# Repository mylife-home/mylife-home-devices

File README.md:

# mylife-home-devices
MyLife Home devices

- [ePanel IO](epanel-io/README.md) :white_check_mark: Module de tableau électrique pour interconnecter E/S avec domotique (rpi/esp)
- [ePanel Energy Monitor](epanel-energy-monitor/README.md) :white_check_mark: Module de tableau électrique pour mesurer la consommation électrique
- [ePanel Controller](epanel-controller/README.md) :white_check_mark: Module de tableau électrique pour contrôler IO et Energy Monitor
- [Garden box](garden-box/README.md) :white_check_mark: Boîtier de commandes/capteurs dans le jardin
- [RGB garden box](rgb-garden-box/README.md) :white_check_mark: Boîtier de commande spots RGB dans le jardin
- [RGB spot 10W](rgb-spot-10w/README.md) :white_check_mark: Reprise de spots existant infrarouge pour connexion direct cables RGB
- [Garage door driver](garage-door-driver/README.md) :white_check_mark: Pilote de porte de garage
- [Clim driver](clim-driver/README.md) :white_check_mark: Pilote de clim
- [Gate driver](gate-driver/README.md) :hourglass: Pilote de portail
- [Bed Smart Plug](bed-smart-plug/README.md) :white_check_mark: "Multiprise intelligente" pour mettre en tête de lit
- [Presence Wifi sensor](presence-wifi-sensor/README.md) :question: Détecteur de présence Wifi
- [RGB LED inverter](rgb-led-inverter/README.md) :no_entry: common anode -> common cathode
- RGB indoor box :question: Boîtier de commande spots/ruban leds RGB en intérieur
- Kitchen hood driver :question: Pilote de hôte
- Pergola driver :question: Pilote de pergola (ZETA 868 ?)
- [Fairy lights](fairy-lights/README.md): :hourglass: guirlande de noël
- [Heater driver](heater-driver/README.md): :question: pilote de radiateur
- [Deco light](deco-light/README.md): :question: Lumière de décoration

## Notes
- Tutorial KiCad: https://www.youtube.com/playlist?list=PLuQznwVAhY2WA4CIf3_aB_e8hRCSbQuUp
- Best practice routing PCB: https://resources.altium.com/fr/p/top-5-pcb-design-guidelines-every-pcb-designer-needs-know
- Kicad to JLCPCB
  - https://support.jlcpcb.com/article/149-how-to-generate-gerber-and-drill-files-in-kicad
  - https://support.jlcpcb.com/article/84-how-to-generate-the-bom-and-centroid-file-from-kicad
  - plugin pour aide a la generation de commande : https://github.com/Bouni/kicad-jlcpcb-tools
  - plugin pour importer les composants JLCPCB dans Kicad : https://github.com/TousstNicolas/JLC2KiCad_lib
- Component footprints : https://componentsearchengine.com/
- ESP32-POE:
  - NE PAS utiliser GPIO0 si possible (ne pas le mettre DOWN au boot)
  - Attention : Version avec antenne interne est plus grande (pas que l'ESP, toute la board). Le footprint Kicad courant correspond à la version avec antenne externe : 
- ESP8266 strapping pins:
  - GPIO0, GPIO1, GPIO2: boot failure if pulled LOW
  - GPIO15: boot failure if pulled HIGH
  - GPIO1, GPIO2, GPIO3, GPIO9, GPIO10, GPIO16: pin is high at BOOT

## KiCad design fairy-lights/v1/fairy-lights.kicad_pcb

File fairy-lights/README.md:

# Fairy lights

## Besoin

- Avec Eléonore
- Guirlande pour sapin
- Intégré ESPHome

## Design

- Guirlande :
  - WS2812B
  - https://amzn.eu/d/6PvWFXF
  - ( https://www.adafruit.com/product/4917 )
- Contrôleur :
  - WeMos D1 mini, sur gpio3 pour DMA
  - config esphome dma -> GPIO3 - RX
- Alimentation :
  - Puissance guirlande : Alim 5V 6A -> 60ma / led
  - ~alim 6A (69.5x39x24) : https://fr.rs-online.com/web/p/alimentations-a-decoupage/1358945~
  - ~alim 8A (87x52x29.5) : https://fr.rs-online.com/web/p/alimentations-a-decoupage/1358955~
  - alime externe 5V 8A : https://www.amazon.fr/dp/B088FBXTPS : `+` au milieu `-` à l'extérieur, 5.5mm - 2.5mm
  - Connecteur : 
    - https://fr.rs-online.com/web/p/connecteurs-d-alimentation-dc/2832406 - 283-2406
    - ( https://fr.rs-online.com/web/p/connecteurs-d-alimentation-dc/8782606 )
- IRLZ44N pour switch l'alim (sans heatsink), sortie esp direct sur Din LEDs : https://fr.rs-online.com/web/p/transistors-mosfet/5410086 541-0086
- Boitier : https://fr.rs-online.com/web/p/boitiers-pour-usage-general/9190373 - 919-0373

## V1

### Wiring

- `+` -> fil avec points noirs
- `D` -> fil du milieu
- `-` -> fil de l'autre côté 

### 3D view

### Main

### Images

## Prototype 1

- Sur breadboard
- Verifier qu'on peut piloter la guirlande avec esp8366/esphome

### Pinout de la guirlande

- `+` -> fil avec points noirs
- `D` -> fil du milieu
- `-` -> fil de l'autre côté

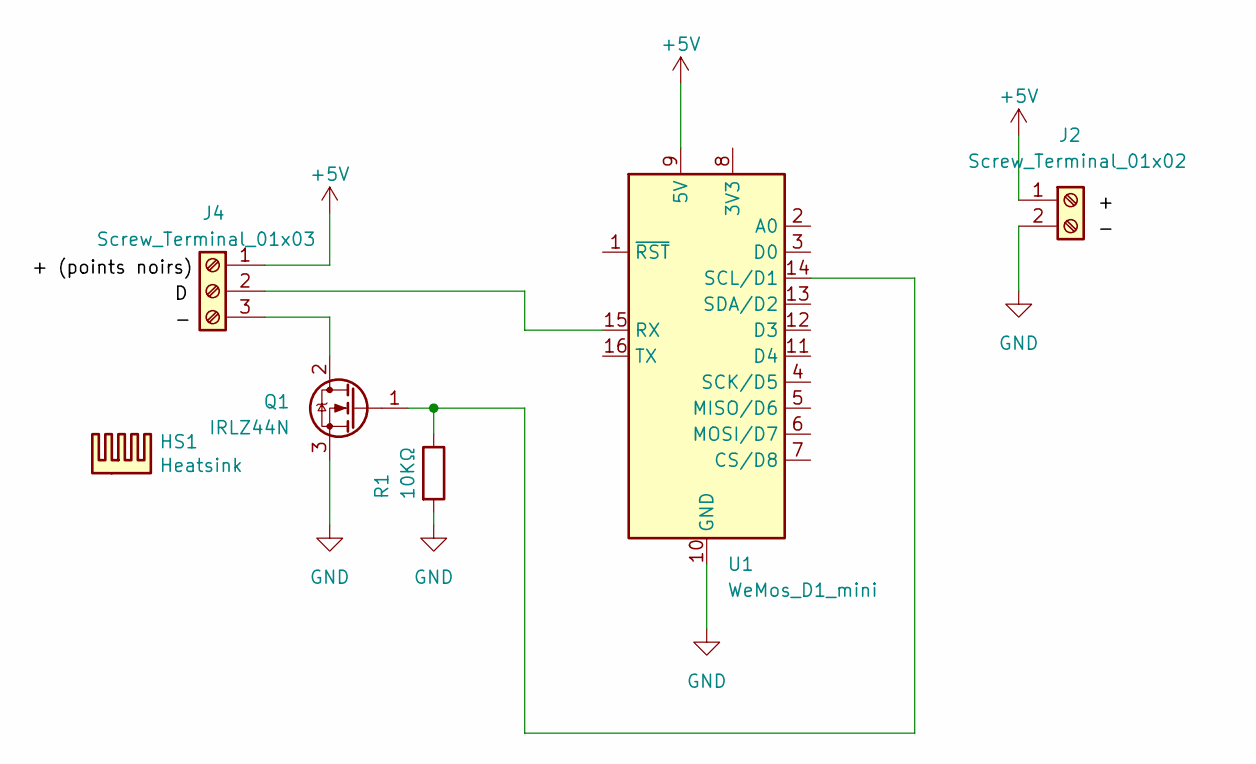
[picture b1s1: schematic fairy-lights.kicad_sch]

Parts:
HS1: Heatsink; Heatsink_Fischer_SK104-STC-STIC_35x13mm_2xDrill2.5mm
J2: Screw_Terminal_01x02; TerminalBlock_bornier-2_P5.08mm
J4: Screw_Terminal_01x03; TerminalBlock_bornier-3_P5.08mm
Q1: IRLZ44N; TO-220-3_Vertical
R1: 10KΩ; R_Axial_DIN0207_L6.3mm_D2.5mm_P15.24mm_Horizontal
U1: WeMos_D1_mini; WEMOS_D1_mini_light

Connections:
+5V: J2.1, J4.1, U1.9 (5V)
GND: J2.2, Q1.3 (S), R1.2, U1.10 (GND)
unnamed: J4.2, U1.15 (RX)
unnamed: J4.3, Q1.2 (D)
unnamed: Q1.1 (G), R1.1, U1.14 (SCL/D1)

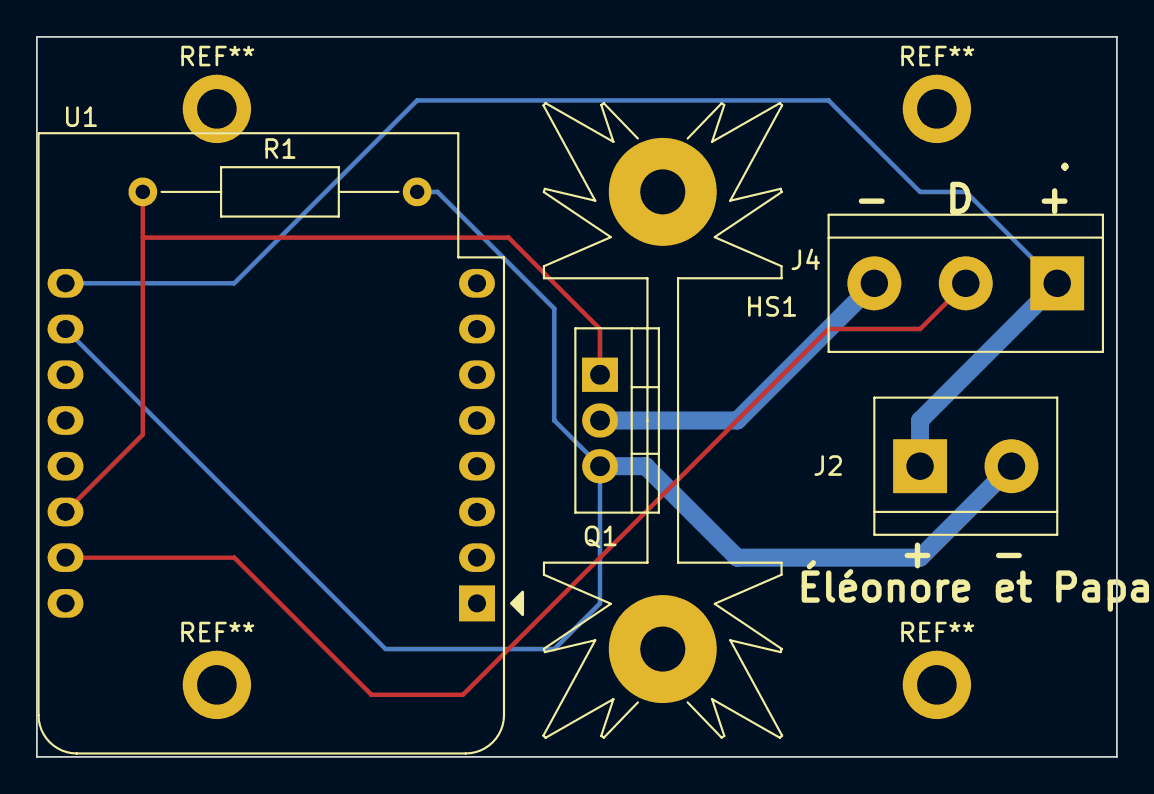
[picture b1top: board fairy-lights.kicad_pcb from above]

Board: 2 copper layers, 60.0 x 40.0 mm, 6 parts (0 on the bottom side), 5 nets.

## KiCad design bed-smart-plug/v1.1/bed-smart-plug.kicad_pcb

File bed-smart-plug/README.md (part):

# Bed Smart Plug

## Besoin

- Récepteur 433mhz (pour télécommande)
- Capteur température
- 4 sorties prises entre 5W et 200W
- Wifi et Ethernet
- Boitier :
  - peut etre relativement large/long, mais plat
  - avec les prises sur un côté
  - comme un switch
  - comme ca on peut le mettre sous un meuble, ou derriere un meuble debout

### Emplacements

- chambre parents
- chambre Eléonore
- chambre Éloïse
- chambre d'amis ?
- rdc derrière TV ?
- bibliothèque pour lampe pot de fleurs + température ?

## Choix techniques

- ESP32 ethernet ou wifi
  - prévoir des trous sur le PCB pour fixer l'esp avec un serre flex entre son header et son module ESP, sur l'inscription "ESP32-PoE"
- SSR pour éviter claquement relais
  - BT136 (4A max)
  - Dissipateurs
  - Fusible 5x20 à souder
- Entree Prise alim IEC C14
- Sorties prises IEC C13 pour avoir un format plus compact
- Capteur température :
  - DS18b20
  - avec Jack
  - possible souder jack a la main sinon
  - capteur integré inutile (mesure la temperature de l'esp/des triac pas de la piece)
- Télécommande 433MHz:
  - Renkforce 1208459
  - https://amzn.eu/d/fGBrWJP
  - https://www.conrad.fr/fr/p/renkforce-1208459-sans-fil-telecommande-interieure-1208459.html

## Design

- Board : ESP32-POE https://www.olimex.com/Products/IoT/ESP32/ESP32-POE/open-source-hardware
- Alim 220v -> 5V 1A : 
  - ~~https://fr.rs-online.com/web/p/alimentations-a-decoupage/1812200~~ (n'existe plus)
  - https://fr.rs-online.com/web/p/alimentations-a-decoupage/1359226
- Jack DS18B20 :
  - https://www.amazon.fr/dp/B075FYYLLV/
  - https://fr.rs-online.com/web/p/connecteurs-jacks/5051299
- Récepteur 433MHz : (modulation ASK)
  - ~~AM-RX12A-433P https://fr.farnell.com/rf-solutions/am-rx12a-433p/recepteur-module-rf-433-92-110dbm/dp/2759279~~ (frais de gestion trop chers)
  - QAM-RX10-433 https://fr.rs-online.com/web/p/modules-rf/1258208
  - pinout compatible
  - normalement 5V, tester en broadboard avec alim 5V + pont diviseur sur les data pour passer a 3.3V
- Triac : BT136-600E https://fr.rs-online.com/web/p/triac/7271120
  - ~~Dissipateur https://fr.rs-online.com/web/p/dissipateurs-de-chaleur/1898101/~~
  - moins haut, même base : https://fr.rs-online.com/web/p/dissipateurs-de-chaleur/1898094
  - vis M3 : même que garden box : https://fr.rs-online.com/web/p/vis-a-rondelle-indesserrable/0279149
  - écrous M3 : https://fr.rs-online.com/web/p/ecrous-hexagonaux/0560293
- Porte fusible : https://fr.rs-online.com/web/p/porte-fusibles/1769047
  - Fusible : https://fr.rs-online.com/web/p/fusibles-cartouches/6686007
- Boitier :
  - https://fr.rs-online.com/web/p/boitiers-pour-usage-general/8180494
    - noir comme les connecteurs C13/C14
    - les facades laterales sont d'un seul tenant: le couvercle est "plat", plus facile pour percer les facades.
  - Vis de fixation PCB : https://fr.rs-online.com/web/p/vis-autotaraudeuses/4831202
- Prises :
  - ~~entree C14 : https://fr.rs-online.com/web/p/connecteurs-iec/8117207~~
  - ~~sortie C13 : https://fr.rs-online.com/web/p/connecteurs-iec/8117193~~
  - sortie C13 x 4 à clip : https://fr.rs-online.com/web/p/connecteurs-iec/2318101
    - couper une barre (phase), laisser les 2 autres
    - montage :

  - entrée C13 à clip : https://fr.rs-online.com/web/p/connecteurs-iec/0481623
    - montage :

  - ~~1 entrée 4 sorties : https://fr.rs-online.com/web/p/connecteurs-iec/3135474~~
    - semble indisponible

  - Prise C14 pour câbles : https://amzn.eu/d/47d2yMY

## Observations Prototype-1 epanel-io

- cf [epanel-io/README.md#observations](../epanel-io/README.md#observations) - Triac
- si on enleve snubber du phototriac, toujours une fuite (couper la piste entre C3 et C4)
- si on enleve les 2 snubbers, plus de fuite, spot led 10w reste eteint (couper la piste entre C3 et le triac)

## Prototype-1

### Objectifs

- Triac: 
  - dissipateurs
  - snubbers/bruit/fuite
    - spot 10w
    - guirlande boules
    - lampe bureau
    - lampe chevet
    - alim a decoupage
- 433MHz receiver
  - binding avec telecommandes
- ds18b20
  - jack pinout: voir quelles broches sur chaque prise matchent + selectionner le pinout qu'on veut.
- fusibles

### Schematic

- [Schematic](prototype-1/schematic.png)

### Pinout

- GPIO02 : Triac
- GPIO13 : DS18B20
- GPIO36 : Récepteur 433MHz

### Observations

- Dissipateur :
  - Rapprocher dissipateur et triac de 0.5 - 1 mm
  - Fixation dissipateur/triac : écrou M3 + reprendre vis M3 anti-deserrage garden-box
- Fusibles : OK
- Triac :
  - spot 10w :
    - triac snubber => fuite (KO)
    - opto snubber => fuite (KO)
    - sans snubber => pas de bruit (OK)
  - Perceuse à colonne :
    - puissance : 1.6A au démarrage puis 0.8
    - Avec/Sans snubber : pas de bruit mais la perceuse fait elle du bruit
    - apres 5 mins dissipateur + triac froids 
  - Lampe chevet Éloïse
    - puissance : 26.5ma
    - Avec snubber : KO bruit quand off
    - Sans snubber : OK sans bruit
  - Guirlande Éloïse
    - Avec snubber : KO clignote
    - Sans snubber : OK sans bruit
    - puissance très instable semble avec des pics a 600ma puis revient a 0ma (problème multimètre ?)
  - Lampe bureau
    - puissance semble 25ma (problème multimètre ?)
    - Avec snubber : KO bruit quand off
    - Sans snubber : OK sans bruit
  - Lampe chevet Eléonore
    - puissance 1.5a???? (problème multimètre ?) -> Ampoule à incandescence 40W
    - Avec snubber : OK sans bruit
    - Sans snubber : OK sans bruit
- Prise jack 

  (de gauche à droite) 
  - 1 : corps
  - 2 : pin penché 
  - 3 : base pin central
  - 4 : extrémité pin central

  Attention : bien enfoncer la prise
  - On peut mettre la prise sous l'ESP

- Récepteur 433mhz
  - Les 2 pins data sont reliés ensemble 
  - Connecter au 5V, et mettre un point diviseur :
    - R1 = 10k (entre output recepteur et input ESP)
    - R2 = 2x 10k en série (entre input ESP et GND)
  - Config dump : 
```yaml
    remote_receiver:
      pin: GPIO36
      dump:
      - rc_switch
      tolerance: 50%
      filter: 250us
      idle: 4ms
      buffer_size: 2kb
```
  - Valeurs (le repeat est très rapproché) : 
    - `Received RCSwitch Raw: protocol=1 data='...'`
  
  _Config télécommande grise : 1 = ON, 5 = ON_
  
| Action | code télécommande | code ABCD | ?? | on/off |
|---|---|---|---|---|
| A on   | 00 01 01 01 00 | 00 01 01 01 | 01 | 00 01 |
| A off  | 00 01 01 01 00 | 00 01 01 01 | 01 | 01 00 |
| B on   | 00 01 01 01 00 | 01 00 01 01 | 01 | 00 01 |
| B off  | 00 01 01 01 00 | 01 00 01 01 | 01 | 01 00 |
| C on   | 00 01 01 01 00 | 01 01 00 01 | 01 | 00 01 |
| C off  | 00 01 01 01 00 | 01 01 00 01 | 01 | 01 00 |
| D on   | 00 01 01 01 00 | 01 01 01 00 | 01 | 00 01 |
| D off  | 00 01 01 01 00 | 01 01 01 00 | 01 | 01 00 |

  _Config télécommande blanche : 1 = ON, 2 = ON_

  => Code télécommande : `00 00 01 01 01`, le reste semble correspondre

  - Avec récepteur dans salon :
    - Fontionne depuis CH1
    - Fonctionne depuis CHP

  _Config télécommande renkforce : pos 1_

| Action | code télécommande | code ABCD | ?? | on/off |
|---|---|---|---|---|
| 1 on   | 00 01 01 01 | 00 01 01 01 01 | 01 | 01 01 |
| 1 off  | 00 01 01 01 | 00 01 01 01 01 | 01 | 01 00 |
| 2 on   | 00 01 01 01 | 01 00 01 01 01 | 01 | 01 01 |
| 2 off  | 00 01 01 01 | 01 00 01 01 01 | 01 | 01 00 |
| 3 on   | 00 01 01 01 | 01 01 00 01 01 | 01 | 01 01 |
| 3 off  | 00 01 01 01 | 01 01 00 01 01 | 01 | 01 00 |
| 4 on   | 00 01 01 01 | 01 01 01 00 01 | 01 | 01 01 |
| 4 off  | 00 01 01 01 | 01 01 01 00 01 | 01 | 01 00 |

## Prototype-2

### Objectifs

- boitier 
- sortie RJ45
- sortie prise jack
- fixations C13/C14
- tester nouveau dissipateur

### Observations

- Dissipateur + écrou de fixation OK
- Boîtier :
  - pas assez long (on ne peut pas mettre toutes les prises + ESP)
  - pas assez large (ESP ne tient pas en largeur)
  - hauteur OK mais prise C14 avec vis sur les côtés ne tient pas en hauteur : voir pour prendre une encastrable comme la multiprise C13
  - aluminium pour ne pas se déformer avec les trous ?
  - aérations ?
  - **aluminium trop cher, autres boitiers mauvaise taille. On garde celui là mais en mettant l'alime/jack/rj45 sur un côté**
- Multiprise C13 x4 : séparation des phases OK

- Perçage boitier pour multiprise C13x4
  - Tracer au cutter + règle métallique
  - Le gros :
    - Découpage disque Dremel vitesse 5 + coins avec perceuse a colonne plus gros forêt placo (faire coins en premier)
  - la finition :
    - tubes ponceuse Dremel, vitesse 2.5
    - gros tube pour partie plate + coins arrondis
    - petit tube pour coin moins arrondis (cf forme des prises)
    - lime pour égaliser
  - Passage des clips (le boitier est trop épais)
    - Entamer l'épaisseur avec gros tube
    - Installation de la prise : pousser les clips vers l'extérieur depuis l'intérieur des prises

  - Tests:
    - branchement/debranchement prise OK
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
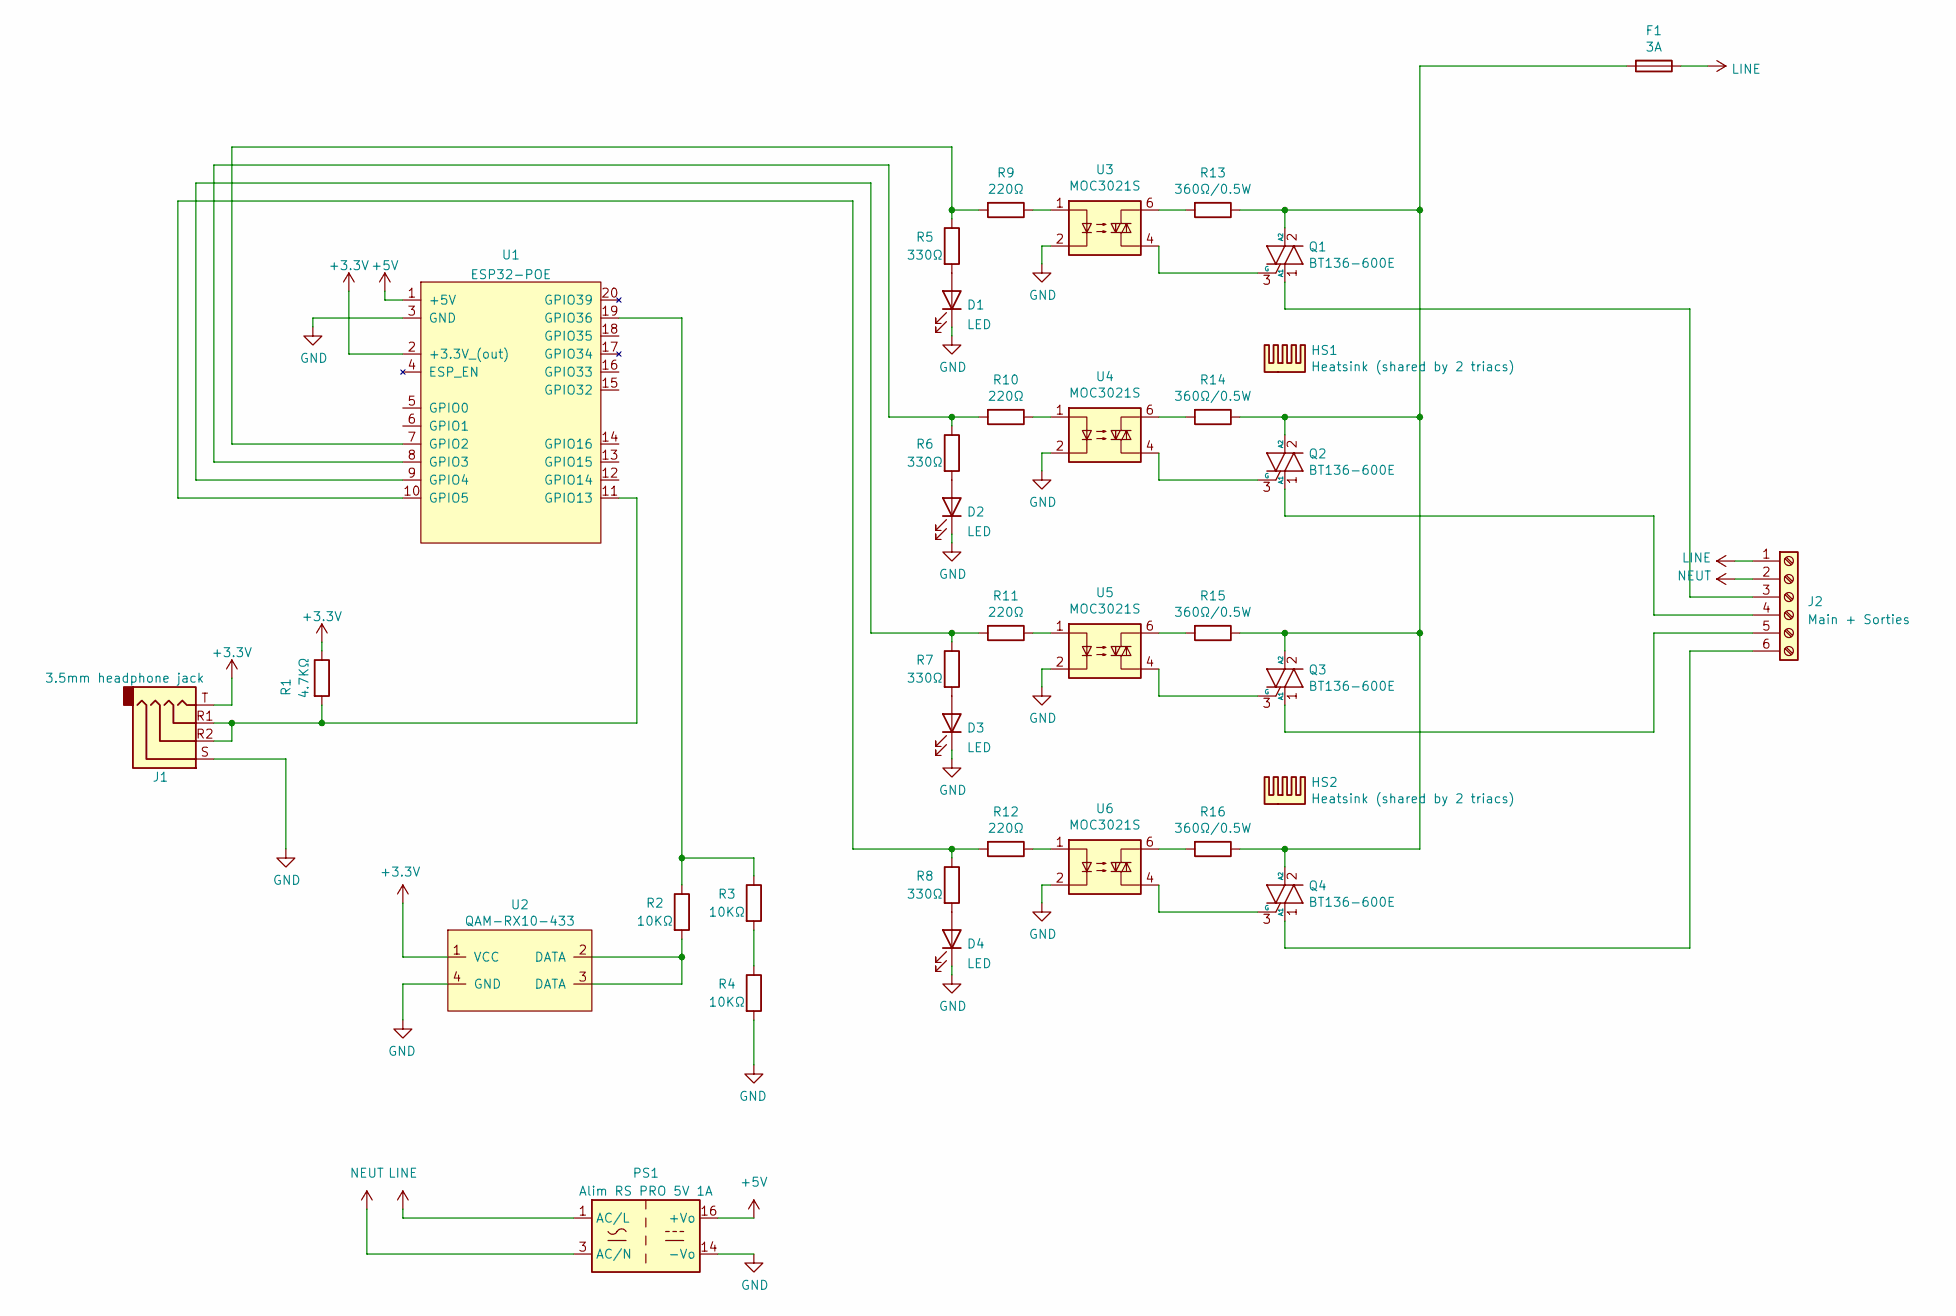
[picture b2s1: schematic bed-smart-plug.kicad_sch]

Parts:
D1, D2, D3, D4: LED; D_0805_2012Metric; LCSC C2297
F1: 3A; Fuseholder_Cylinder-5x20mm_Schurter_0031_8201_Horizontal_Op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
HS1, HS2: Heatsink (shared by 2 triacs); Heatsink_Fischer_SK104-STC-STIC_35x13mm_2xDrill2.5mm
J1: 3.5mm headphone jack; Jack_3.5mm_PJ320D_Horizontal; LCSC C521460
J2: Main + Sorties; TerminalBlock_bornier-6_P5.08mm
PS1: Alim RS PRO 5V 1A; Converter_ACDC_MeanWell_IRM-03-xx_THT
Q1, Q2, Q3, Q4: BT136-600E; TO-220-3_Vertical
R1: 4.7KΩ; R_0402_1005Metric; LCSC C25900
R2, R3, R4: 10KΩ; R_0603_1608Metric; LCSC C4226066
R5, R6, R7, R8: 330Ω; R_0603_1608Metric; LCSC C2918523
R9, R10, R11, R12: 220Ω; R_0603_1608Metric; LCSC C22962
R13, R14, R15, R16: 360Ω/0.5W; R_1210_3225Metric; LCSC C2759574
U1: ESP32-POE
U2: QAM-RX10-433
U3, U4, U5, U6: MOC3021S; SMDIP-6_W9.53mm; LCSC C427436

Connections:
+3V3: J1.T, R1.1, U1.2 (+3.3V_(out)), U2.1 (VCC)
+5V: PS1.16 (+Vo), U1.1 (+5V)
GND: D1.1 (K), D2.1 (K), D3.1 (K), D4.1 (K), J1.S, PS1.14 (-Vo), R4.2, U1.3 (GND), U2.4 (GND), U3.2, U4.2, U5.2, U6.2
LINE: F1.1, J2.1, PS1.1 (AC/L)
NEUT: J2.2, PS1.3 (AC/N)
unnamed: D1.2 (A), R5.2
unnamed: D2.2 (A), R6.2
unnamed: D3.2 (A), R7.2
unnamed: D4.2 (A), R8.2
unnamed: J2.3, Q1.1 (A1)
unnamed: J2.4, Q2.1 (A1)
unnamed: J2.5, Q3.1 (A1)
unnamed: J2.6, Q4.1 (A1)
unnamed: F1.2, Q1.2 (A2), Q2.2 (A2), Q3.2 (A2), Q4.2 (A2), R13.1, R14.1, R15.1, R16.1
unnamed: Q1.3 (G), U3.4
unnamed: Q2.3 (G), U4.4
unnamed: Q3.3 (G), U5.4
unnamed: Q4.3 (G), U6.4
unnamed: R2.2, U2.2 (DATA), U2.3 (DATA)
unnamed: R3.2, R4.1
unnamed: R9.1, U3.1
unnamed: R10.1, U4.1
unnamed: R11.1, U5.1
unnamed: R12.1, U6.1
unnamed: R13.2, U3.6
unnamed: R14.2, U4.6
unnamed: R15.2, U5.6
unnamed: R16.2, U6.6
unnamed: R5.1, R9.2, U1.7 (GPIO2)
unnamed: R6.1, R10.2, U1.8 (GPIO3)
unnamed: R7.1, R11.2, U1.9 (GPIO4)
unnamed: R8.1, R12.2, U1.10 (GPIO5)
unnamed: J1.R1, J1.R2, R1.2, U1.11 (GPIO13)
unnamed: R2.1, R3.1, U1.19 (GPIO36)

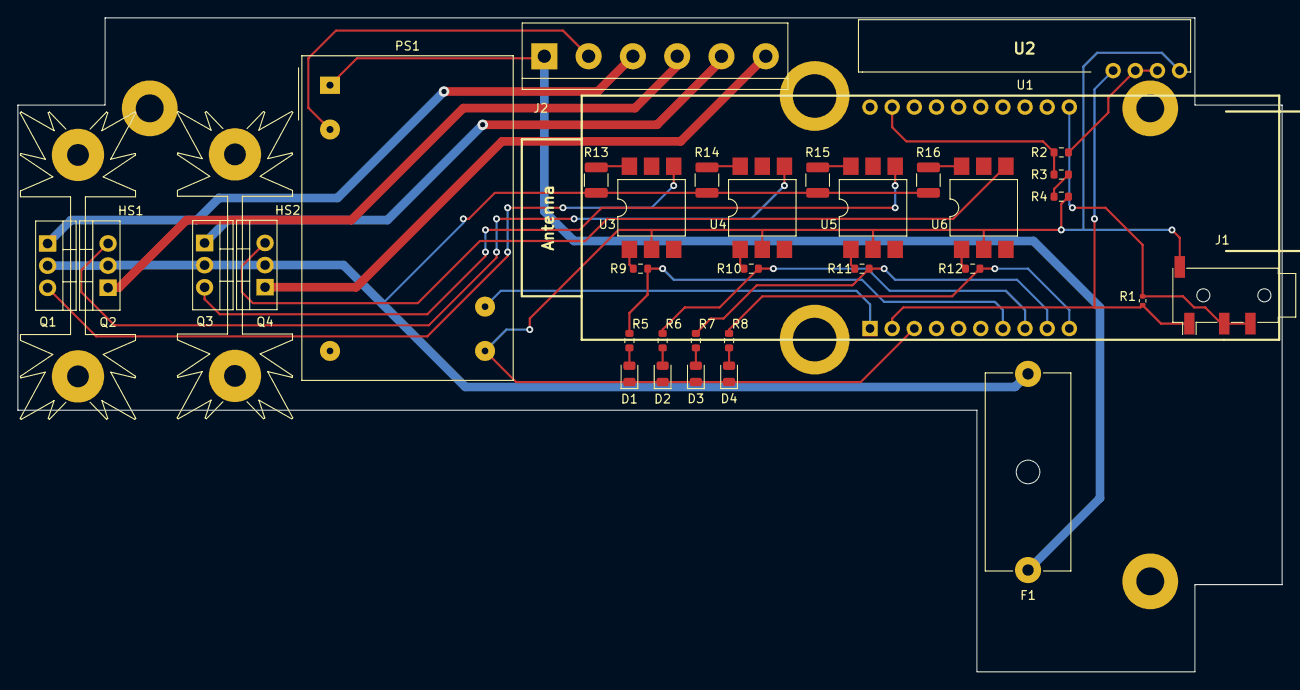
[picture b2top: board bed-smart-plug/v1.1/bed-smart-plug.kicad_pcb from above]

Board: 2 copper layers, 145.0 x 75.0 mm, 36 parts (0 on the bottom side), 34 nets.

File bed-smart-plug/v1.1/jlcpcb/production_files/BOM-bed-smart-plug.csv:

Comment,Designator,Footprint,LCSC
220Ω,"R10,R11,R12,R9",R_0603_1608Metric,C22962
LED,"D1,D2,D3,D4",D_0805_2012Metric,C2297
4.7KΩ,R1,R_0402_1005Metric,C25900
360Ω/0.5W,"R13,R14,R15,R16",R_1210_3225Metric,C2759574
330Ω,"R5,R6,R7,R8",R_0603_1608Metric,C2918523
10KΩ,"R2,R3,R4",R_0603_1608Metric,C4226066
MOC3021S,"U3,U4,U5,U6",SMDIP-6_W9.53mm,C427436
3.5mm headphone jack,J1,Jack_3.5mm_PJ320D_Horizontal,C521460
Main + Sorties,J2,TerminalBlock_bornier-6_P5.08mm,
ESP32-POE,U1,ESP32-POE,
QAM-RX10-433,U2,QAM-RX10-433,
BT136-600E,Q3,TO-220-3_Vertical,
BT136-600E,Q4,TO-220-3_Vertical,
BT136-600E,Q2,TO-220-3_Vertical,
Alim RS PRO 5V 1A,PS1,Converter_ACDC_MeanWell_IRM-03-xx_THT,
Heatsink (shared by 2 triacs),HS1,Heatsink_Fischer_SK104-STC-STIC_35x13mm_2xDrill2.5mm,
BT136-600E,Q1,TO-220-3_Vertical,
Heatsink (shared by 2 triacs),HS2,Heatsink_Fischer_SK104-STC-STIC_35x13mm_2xDrill2.5mm,
3A,F1,Fuseholder_Cylinder-5x20mm_Schurter_0031_8201_Horizontal_Open,

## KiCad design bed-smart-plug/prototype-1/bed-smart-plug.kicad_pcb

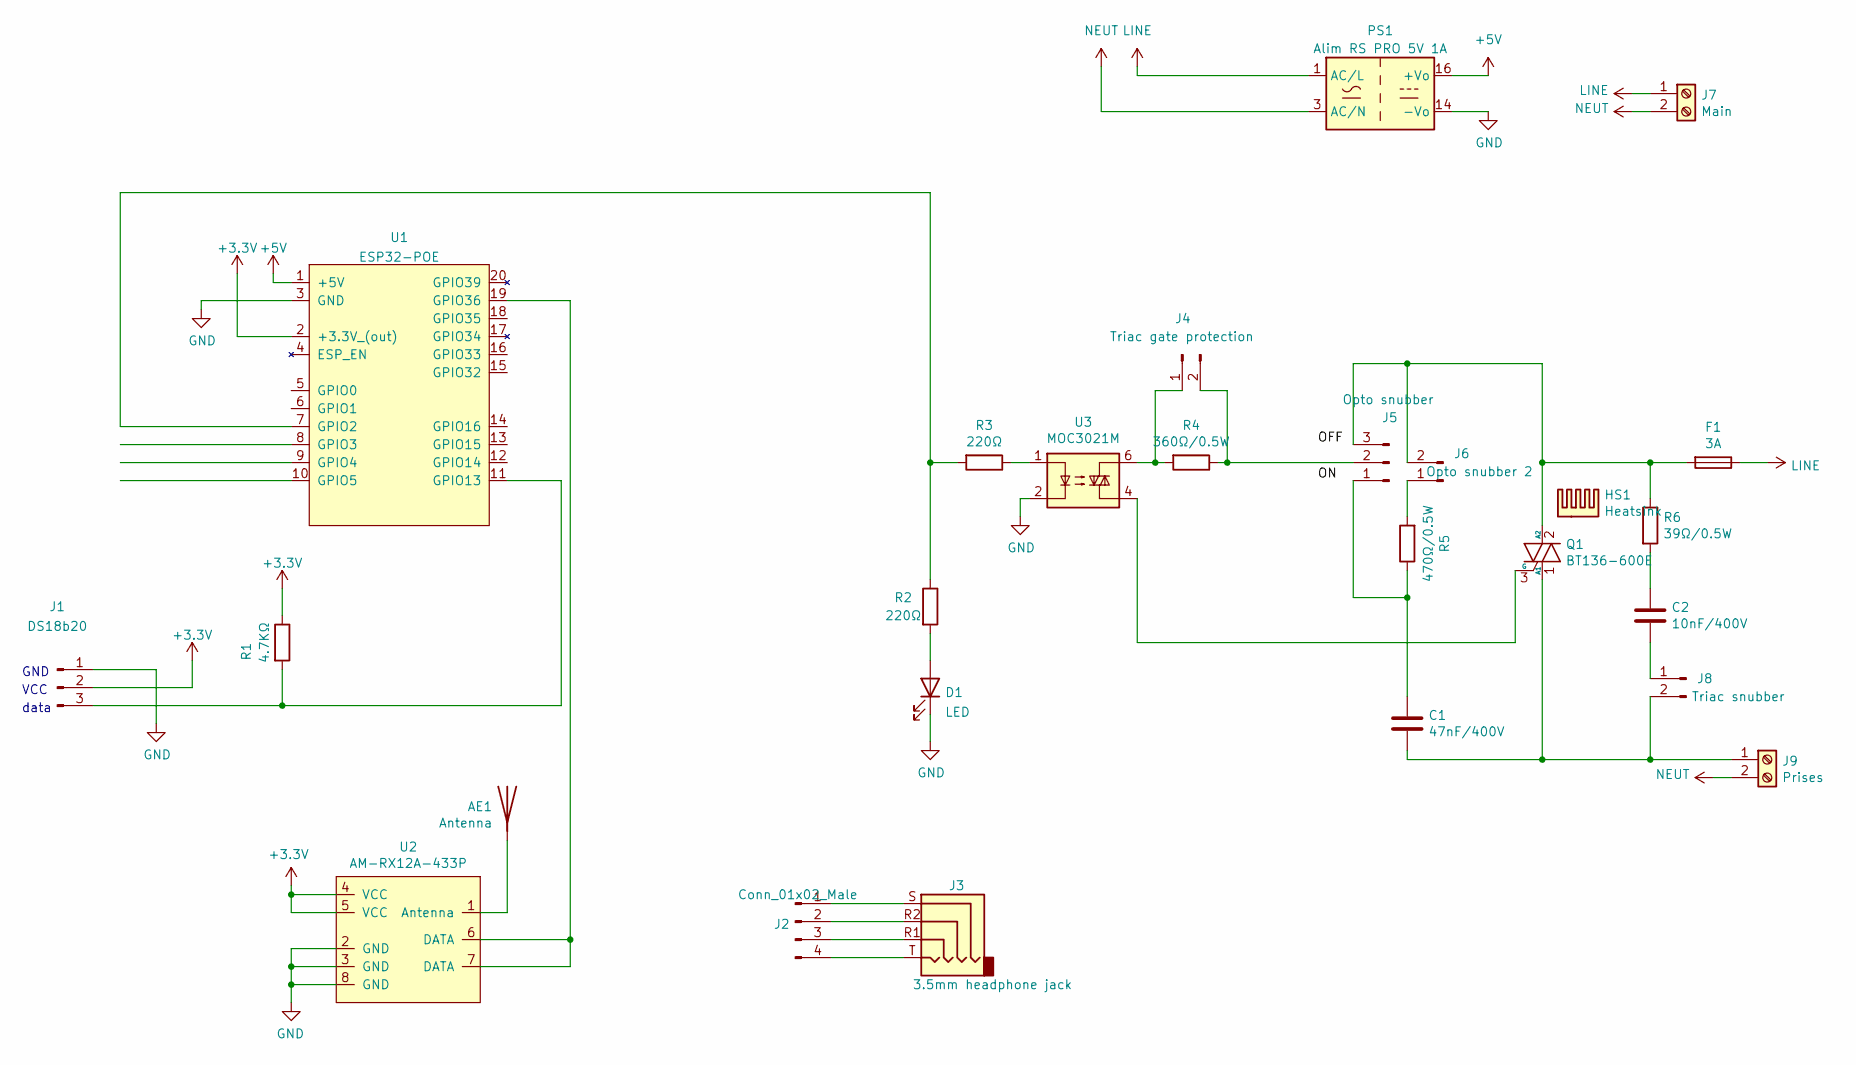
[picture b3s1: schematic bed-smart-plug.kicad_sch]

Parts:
AE1: Antenna; PinHeader_1x01_P2.54mm_Vertical
C1: 47nF/400V; C_1206_3216Metric; LCSC C309031
C2: 10nF/400V; C_0805_2012Metric; LCSC C106840
D1: LED; D_0805_2012Metric; LCSC C2297
F1: 3A; Fuseholder_Cylinder-5x20mm_Schurter_0031_8201_Horizontal_Op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
HS1: Heatsink; Heatsink_Fischer_SK104-STC-STIC_35x13mm_2xDrill2.5mm
J1: DS18b20; PinHeader_1x03_P2.54mm_Vertical
J2: Conn_01x02_Male; PinHeader_1x04_P2.54mm_Vertical
J3: 3.5mm headphone jack; Jack_3.5mm_PJ320D_Horizontal; LCSC C521460
J4: Triac gate protection; PinHeader_1x02_P2.54mm_Vertical
J5: Opto snubber; PinHeader_1x03_P2.54mm_Vertical
J6: Opto snubber 2; PinHeader_1x02_P2.54mm_Vertical
J7: Main; TerminalBlock_bornier-2_P5.08mm
J8: Triac snubber; PinHeader_1x02_P2.54mm_Vertical
J9: Prises; TerminalBlock_bornier-2_P5.08mm
PS1: Alim RS PRO 5V 1A; Converter_ACDC_MeanWell_IRM-03-xx_THT
Q1: BT136-600E; TO-220-3_Vertical
R1: 4.7KΩ; R_0402_1005Metric; LCSC C25900
R2, R3: 220Ω; R_0603_1608Metric; LCSC C22962
R4: 360Ω/0.5W; R_1210_3225Metric; LCSC C2759574
R5: 470Ω/0.5W; R_1210_3225Metric; LCSC C830186
R6: 39Ω/0.5W; R_1210_3225Metric; LCSC C422307
U1: ESP32-POE
U2: AM-RX12A-433P; AMRX12A433P
U3: MOC3021M; SMDIP-6_W9.53mm; LCSC C108500

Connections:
+3V3: J1.2, R1.1, U1.2 (+3.3V_(out)), U2.4 (VCC), U2.5 (VCC)
+5V: PS1.16 (+Vo), U1.1 (+5V)
GND: D1.1 (K), J1.1, PS1.14 (-Vo), U1.3 (GND), U2.2 (GND), U2.3 (GND), U2.8 (GND), U3.2
LINE: F1.1, J7.1, PS1.1 (AC/L)
NEUT: J7.2, J9.2, PS1.3 (AC/N)
unnamed: AE1.1 (A), U2.1 (Antenna)
unnamed: C2.1, R6.2
unnamed: D1.2 (A), R2.2
unnamed: J1.3, R1.2, U1.11 (GPIO13)
unnamed: J2.1, J3.S
unnamed: J2.2, J3.R2
unnamed: J2.3, J3.R1
unnamed: J2.4, J3.T
unnamed: J4.1, R4.2, U3.6
unnamed: J4.2, J5.2, R4.1
unnamed: C1.1, J5.1, R5.1
unnamed: F1.2, J5.3, J6.2, Q1.2 (A2), R6.1
unnamed: J6.1, R5.2
unnamed: C2.2, J8.1
unnamed: C1.2, J8.2, J9.1, Q1.1 (A1)
unnamed: Q1.3 (G), U3.4
unnamed: R3.1, U3.1
unnamed: R2.1, R3.2, U1.7 (GPIO2)
unnamed: U1.19 (GPIO36), U2.6 (DATA), U2.7 (DATA)

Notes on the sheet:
VCC
data
GND

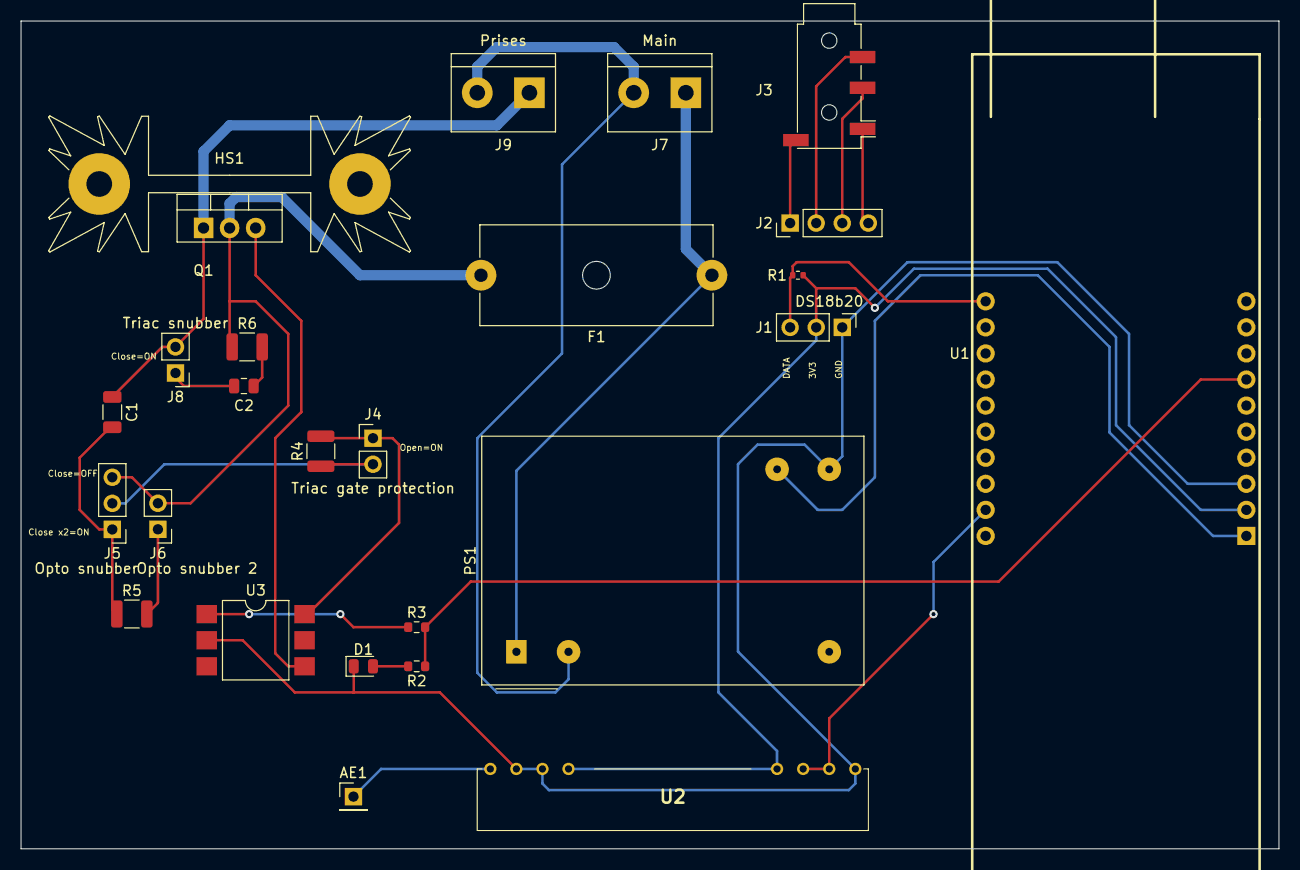
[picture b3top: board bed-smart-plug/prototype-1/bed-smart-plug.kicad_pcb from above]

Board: 2 copper layers, 122.6 x 80.6 mm, 26 parts (0 on the bottom side), 24 nets.

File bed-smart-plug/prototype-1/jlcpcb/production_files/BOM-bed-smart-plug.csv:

Comment,Designator,Footprint,LCSC
10nF/400V,C2,C_0805_2012Metric,C106840
MOC3021M,U3,SMDIP-6_W9.53mm,C108500
220Ω,"R2,R3",R_0603_1608Metric,C22962
LED,D1,D_0805_2012Metric,C2297
4.7KΩ,R1,R_0402_1005Metric,C25900
360Ω/0.5W,R4,R_1210_3225Metric,C2759574
47nF/400V,C1,C_1206_3216Metric,C309031
39Ω/0.5W,R6,R_1210_3225Metric,C422307
3.5mm headphone jack,J3,Jack_3.5mm_PJ320D_Horizontal,C521460
470Ω/0.5W,R5,R_1210_3225Metric,C830186
Conn_01x02_Male,J2,PinHeader_1x04_P2.54mm_Vertical,
Prises,J9,TerminalBlock_bornier-2_P5.08mm,
Triac snubber,J8,PinHeader_1x02_P2.54mm_Vertical,
AM-RX12A-433P,U2,AMRX12A433P,
Opto snubber 2,J6,PinHeader_1x02_P2.54mm_Vertical,
Antenna,AE1,PinHeader_1x01_P2.54mm_Vertical,
Heatsink,HS1,Heatsink_Fischer_SK104-STC-STIC_35x13mm_2xDrill2.5mm,
DS18b20,J1,PinHeader_1x03_P2.54mm_Vertical,
Alim RS PRO 5V 1A,PS1,Converter_ACDC_MeanWell_IRM-03-xx_THT,
ESP32-POE,U1,ESP32-POE,
BT136-600E,Q1,TO-220-3_Vertical,
Opto snubber,J5,PinHeader_1x03_P2.54mm_Vertical,
3A,F1,Fuseholder_Cylinder-5x20mm_Schurter_0031_8201_Horizontal_Open,
Triac gate protection,J4,PinHeader_1x02_P2.54mm_Vertical,
Main,J7,TerminalBlock_bornier-2_P5.08mm,

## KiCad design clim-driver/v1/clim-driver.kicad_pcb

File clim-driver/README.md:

# Clim driver

## Besoin

- Wifi
- doit tenir dans le boitier de clim directement
- alimenté par la clim
- le plus de contrôle possible
- ajouter un capteur de température

### Info clim

- RDC: Toshiba air conditioner RAS-13BKV-E1
- R1: 4x Toshiba air conditioner RAS-05BKV-E
- Telecommande : Toshiba WH-UA01NE
- place derriere capot : 70x15x25
- place pompe relevage :
  - https://www.manomano.fr/p/pompe-relevage-climatisation-mini-orange-230v-aspen-3124579
  - 39x34x80, prévoir sortie cable dans facade 39x34

## Design

- IR send/recv :
  - https://www.wemos.cc/en/latest/_static/files/sch_ir_v1.0.0.pdf
  - https://www.wemos.cc/en/latest/d1_mini_shield/ir.html
  - Led IR: https://fr.rs-online.com/web/p/leds-infrarouges/6997708
  - 18ohm @ 3.3v
- Temp : DS18B2 :
  - en dehors du boitier sinon la temp sera faussée avec la chaleur de l'ESP8266
- Wemos D1 mini :
  - https://www.amazon.fr/dp/B093G72SHN
  - 34x26
- Alim :
  - alim 220v -> 5V 1A : https://fr.rs-online.com/web/p/alimentations-a-decoupage/1812200
  - 37 x 24.5 x 18
  - apparemment il n'existe pas plus petit
- Boitier :
  - https://fr.rs-online.com/web/p/boitiers-pour-usage-general/9190373

## V1

### Wiring

### 3D view

### Main

### Images

| | | |
|---|---|---|
||||
||||

#### CH1

_(pas d'image)_

#### CH2

| | | |
|---|---|---|
||||

#### CH3

| | | |
|---|---|---|
||||

#### CHP

_(pas d'image)_

#### RDC

| | | |
|---|---|---|
||||

### Notes

- Sertissage Dupont : dénuder sur 5mm et ne sertir que le fil conducteur pas la gaine
- Agrandir le trou du boitier à la perceuse à colonne avant de mettre le pas de vis
- Couleurs cable led
  - blanc = +
  - bleu = -
- Couleurs cable DS18B20
  - jaune = IN
  - rouge = 3V3
  - noir = GND

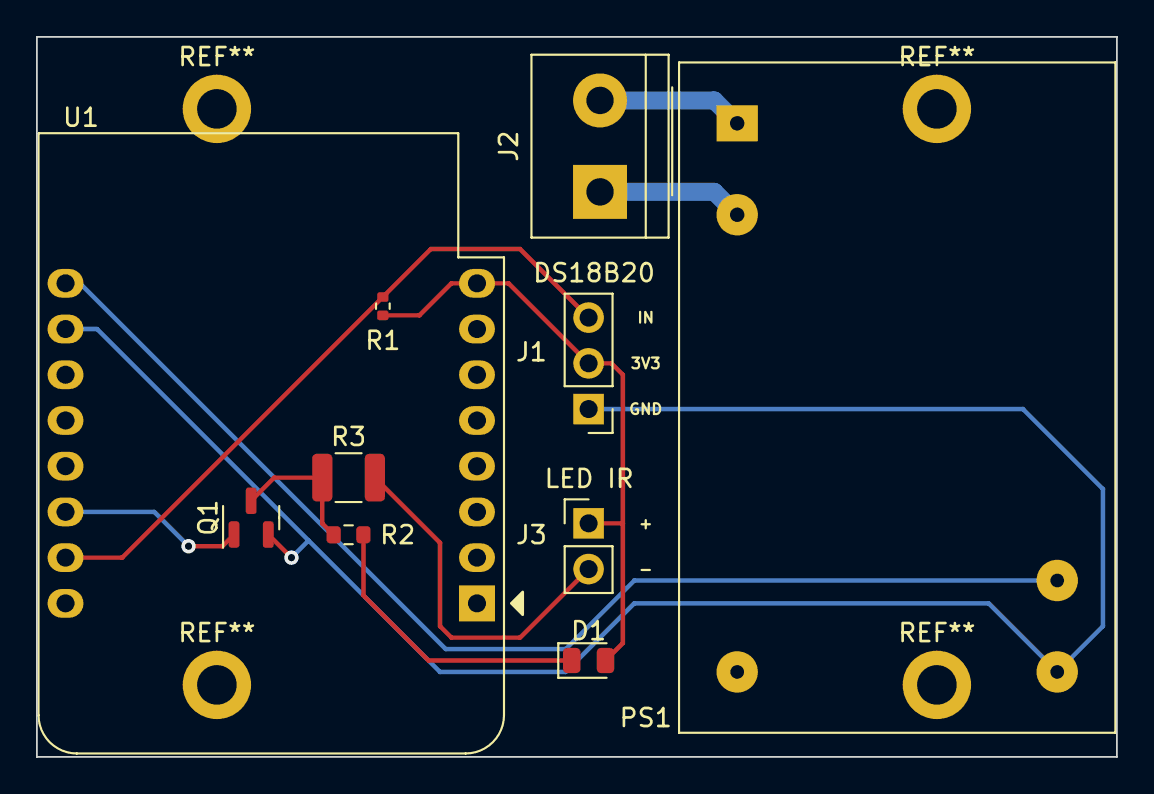
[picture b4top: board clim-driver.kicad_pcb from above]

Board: 2 copper layers, 60.0 x 40.0 mm, 10 parts (0 on the bottom side), 10 nets.

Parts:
D1: LED; D_0805_2012Metric
J1: Conn_01x03_Male; PinHeader_1x03_P2.54mm_Vertical
J2: Screw_Terminal_01x02; TerminalBlock_bornier-2_P5.08mm
J3: Conn_01x02_Pin; PinHeader_1x02_P2.54mm_Vertical
PS1: Alim RS PRO 5V 1A; Converter_ACDC_MeanWell_IRM-03-xx_THT
Q1: BSS138; SOT-23
R1: 4.7KΩ; R_0402_1005Metric
R2: 1KΩ; R_0603_1608Metric
R3: 18Ω/0.5W; R_1210_3225Metric
U1: WeMos_D1_mini; WEMOS_D1_mini_light

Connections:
+3V3: D1.2 (A), J1.2, J3.1, R1.1, U1.8 (3V3)
+5V: PS1.16 (+Vo), U1.9 (5V)
GND: J1.1, PS1.14 (-Vo), Q1.2 (S), U1.10 (GND)
LINE: J2.2, PS1.1 (AC/L)
NEUT: J2.1, PS1.3 (AC/N)
unnamed: D1.1 (K), R2.2
unnamed: J1.3, R1.2, U1.15 (RX)
unnamed: J3.2, R3.2
unnamed: Q1.3 (D), R2.1, R3.1
unnamed: Q1.1 (G), U1.14 (SCL/D1)

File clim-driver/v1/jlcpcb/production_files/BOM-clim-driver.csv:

Comment,Designator,Footprint,LCSC
1KΩ,R2,R_0603_1608Metric,C21190
LED,D1,D_0805_2012Metric,C2297
4.7KΩ,R1,R_0402_1005Metric,C25900
BSS138,Q1,SOT-23,C2938375
18Ω/0.5W,R3,R_1210_3225Metric,C333138
Conn_01x03_Male,J1,PinHeader_1x03_P2.54mm_Vertical,
Screw_Terminal_01x02,J2,TerminalBlock_bornier-2_P5.08mm,
WeMos_D1_mini,U1,WEMOS_D1_mini_light,
Conn_01x02_Pin,J3,PinHeader_1x02_P2.54mm_Vertical,
Alim RS PRO 5V 1A,PS1,Converter_ACDC_MeanWell_IRM-03-xx_THT,

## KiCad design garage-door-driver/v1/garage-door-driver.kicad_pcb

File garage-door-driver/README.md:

# Garage door driver

## Besoin

- doit tenir dans le boitier de la porte ou a côté avec un cable de commande qui sort du boitier
- Wifi
- alimenté par l'alim de la porte
- le plus de contrôle possible
- ajouter un capteur de température

### Fonctionnement de la porte

- Documentation:
  https://www.tubauto.fr/app/uploads/2018/02/procom7-3-fr.pdf

- Moteur garage:

| | | |
|---|---|---|
||||
||||

- Notes:
  - 4 borniers à gauche (comme matériel HiFi)
    - 2 à gauche : alimentation 13V
    - 2 à droite : poussoir déclencheur externe (24v)
  - 2 borniers noirs
    - Sortie (relais d'option) (24v)
      réglage DIL A=OFF B=ON => fin de course (signal ON si porte fermée, OFF sinon)
  - 4 borniers à droite
    - de gauche à droite : 20 - 21 - 5 - 23
    - 20 commun
    - 21-20 => poussoir ouverture totale (4.8v)
    - 5-20 alimentation 24v
    - 23-20 => poussoir ouverture partielle (4.8v)
  - Alimentation moteur:
    - +24v quand montée
    - -24v quand descente

## Design

- Board
  - Wemos D1 mini (ESP8266) 
  - https://amzn.eu/d/irlLEVS
- Alim
  - connexion au 24v
  - https://fr.rs-online.com/web/p/regulateurs-a-decoupage/1934004
  - regarder datasheet pour condensateurs à rajouter
- Borniers
  - https://fr.rs-online.com/web/p/borniers-pour-circuits-imprimes/7901098
- outputs x2 (ouverture partielle/totale)
  - 4.8v vers un commun qui semble etre GND, semble parfait pour sortie transistor
  - 4n35 (1.3v 10ma) https://fr.farnell.com/vishay/4n35/optocoupleur-phototransistor-5000vrms/dp/1328375
  - GPIO 3.3v => R=220ohm
- inputs x3 (moteur double sens, relais d'option)
  - 24v
  - 4n35 (1.3v 10ma) https://fr.farnell.com/vishay/4n35/optocoupleur-phototransistor-5000vrms/dp/1328375
  - 24v => R=2.2kohm
- fixation/layout PCB
  - PCB avec pin header (1 pin sur 2 pour pas de 5.08)
  - les pins headers sont serrés dans les 4 borniers à droite
  - prévoir borniers + fils pour les 2 borniers du milieu
  - taille
    - pin headers vers bord 2.54mm
    - pin headers vers dégagement 1.5cm
    - bord droit retrait degradé sur 1 cm
    - Épaisseur PCB ok des 2 côtés (hauteur/profondeur)
    - H totale = 5cm
    - L totale = 9.5cm

## V1

### Wiring

- GPIO14 - D5 : in moteur (active low)
- GPIO12 - D6 : in moteur (active low)
- GPIO13 - D7 : in porte fermée (active low)
- GPIO4 - D2 : out ouverture partielle
- GPIO5 - D1 : out ouverture totale
- GPIO3 - RX : DS18B20

### 3D view

### Main

### Images

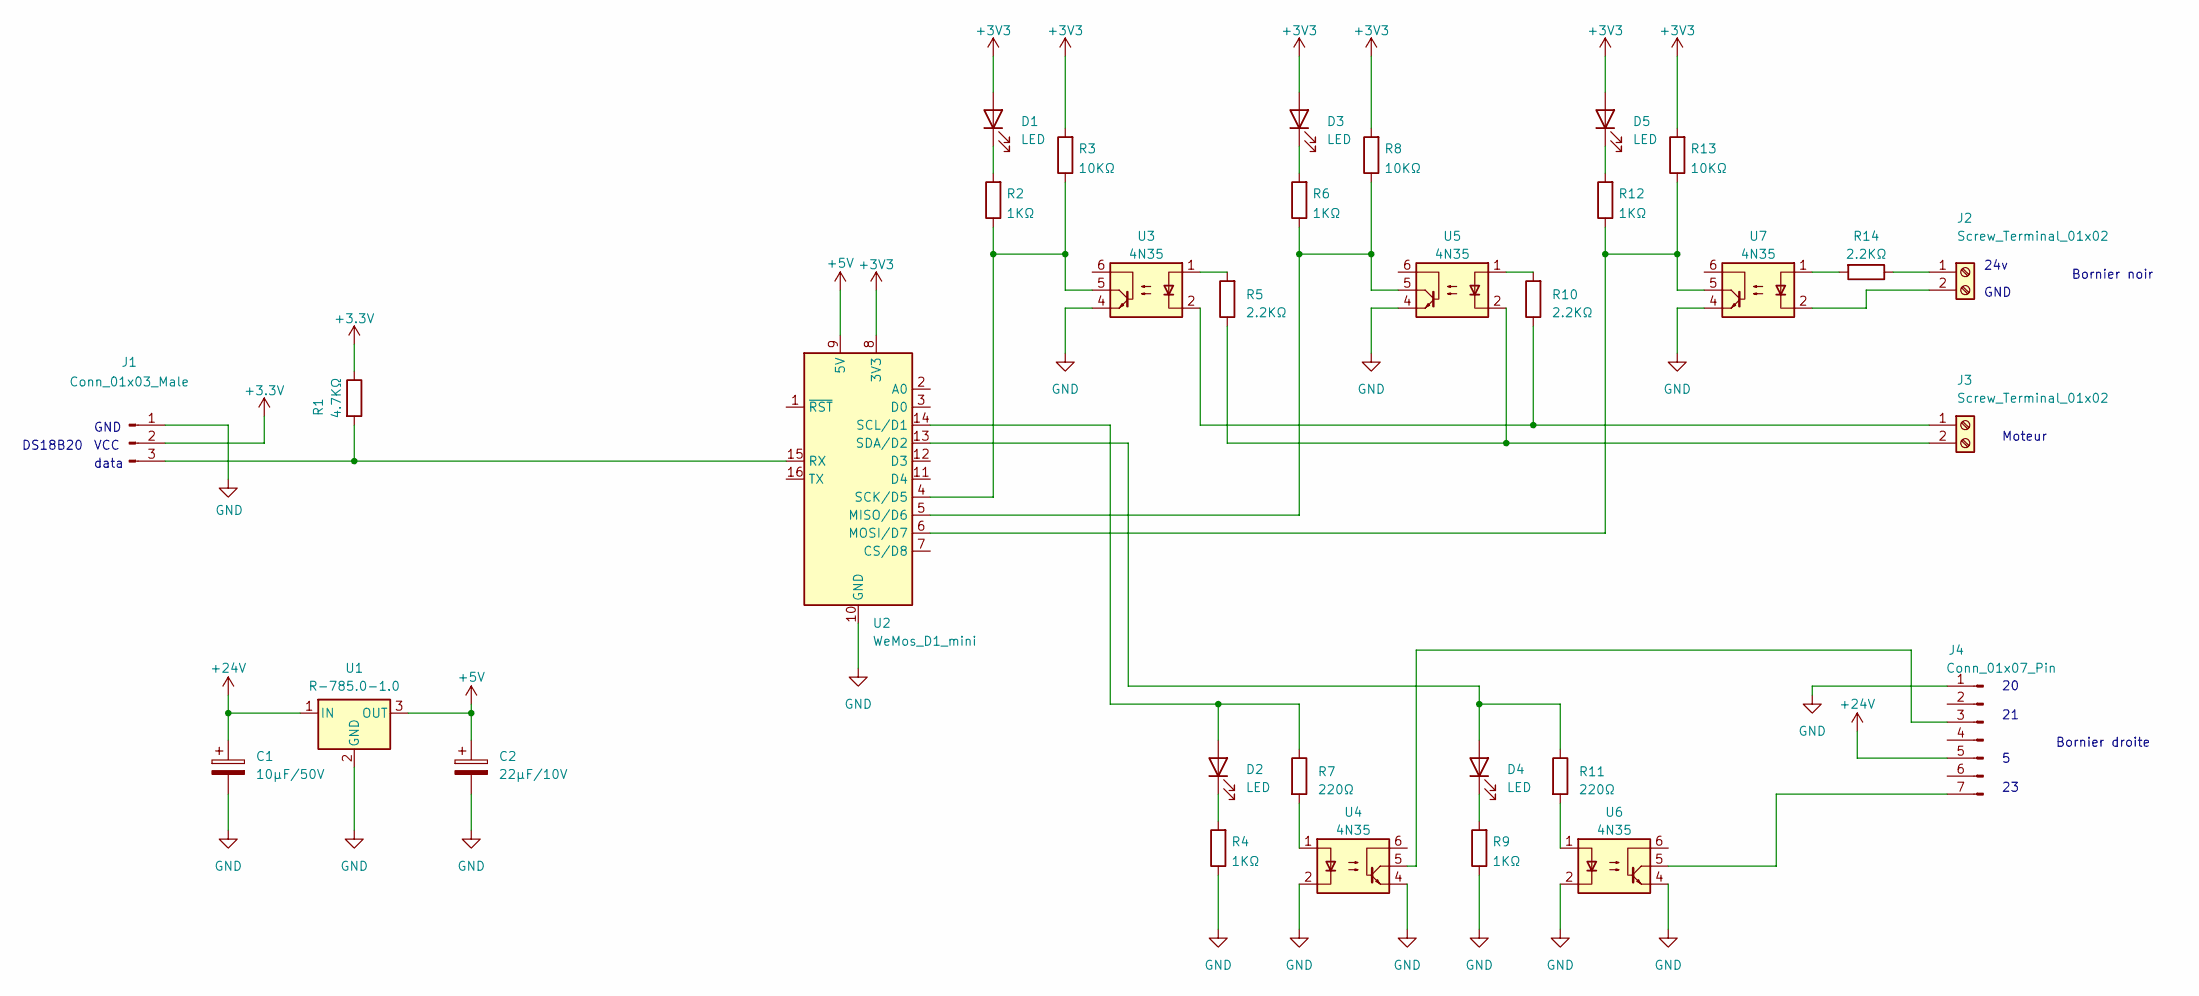
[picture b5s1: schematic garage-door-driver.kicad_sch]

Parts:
C1: 10μF/50V; C_1206_3216Metric; LCSC C417124
C2: 22μF/10V; C_0805_2012Metric; LCSC C92814
D1, D2, D3, D4, D5: LED; D_0805_2012Metric; LCSC C2297
J1: Conn_01x03_Male; PinHeader_1x03_P2.54mm_Vertical
J2, J3: Screw_Terminal_01x02; RS PRO Terminal Small x2
J4: Conn_01x07_Pin; PinHeader_1x07_P2.54mm_Vertical
R1: 4.7KΩ; R_0402_1005Metric; LCSC C25900
R2, R4, R6, R9, R12: 1KΩ; R_0603_1608Metric; LCSC C21190
R3, R8, R13: 10KΩ; R_0603_1608Metric; LCSC C25804
R5, R10, R14: 2.2KΩ; R_0603_1608Metric; LCSC C176136
R7, R11: 220Ω; R_0603_1608Metric; LCSC C22962
U1: R-785.0-1.0; Converter_DCDC_RECOM_R-78E-0.5_THT
U2: WeMos_D1_mini; WEMOS_D1_mini_light
U3, U4, U5, U6, U7: 4N35; DIP-6_W8.89mm_SMDSocket_LongPads; LCSC C500385

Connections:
+5V: C2.1, U1.3 (OUT), U2.9 (5V)
+24V: C1.1, J4.5, U1.1 (IN)
GND: C1.2, C2.2, J1.1, J4.1, R4.1, R9.1, U1.2 (GND), U2.10 (GND), U3.4, U4.2, U4.4, U5.4, U6.2, U6.4, U7.4
unnamed: D1.1 (K), R2.2
unnamed: D2.2 (A), R7.1, U2.14 (SCL/D1)
unnamed: D2.1 (K), R4.2
unnamed: D3.1 (K), R6.2
unnamed: D4.2 (A), R11.1, U2.13 (SDA/D2)
unnamed: D4.1 (K), R9.2
unnamed: D5.1 (K), R12.2
unnamed: J1.3, R1.2, U2.15 (RX)
unnamed: J2.1, R14.1
unnamed: J2.2, U7.2
unnamed: J3.1, R10.1, U3.2
unnamed: J3.2, R5.1, U5.2
unnamed: J4.3, U4.5
unnamed: J4.7, U6.5
unnamed: R5.2, U3.1
unnamed: R7.2, U4.1
unnamed: R10.2, U5.1
unnamed: R11.2, U6.1
unnamed: R14.2, U7.1
unnamed: R6.1, R8.1, U2.5 (MISO/D6), U5.5
unnamed: R12.1, R13.1, U2.6 (MOSI/D7), U7.5
unnamed: R2.1, R3.1, U2.4 (SCK/D5), U3.5

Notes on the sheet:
Bornier droite
20 21 5 23
GND
Bornier noir
24v
data
VCC
Moteur
DS18B20

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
